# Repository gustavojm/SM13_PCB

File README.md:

# New Fixture Controller #
* Autor: DEEE
* GSPC

Poncho para la CIAA NXP con los RDC

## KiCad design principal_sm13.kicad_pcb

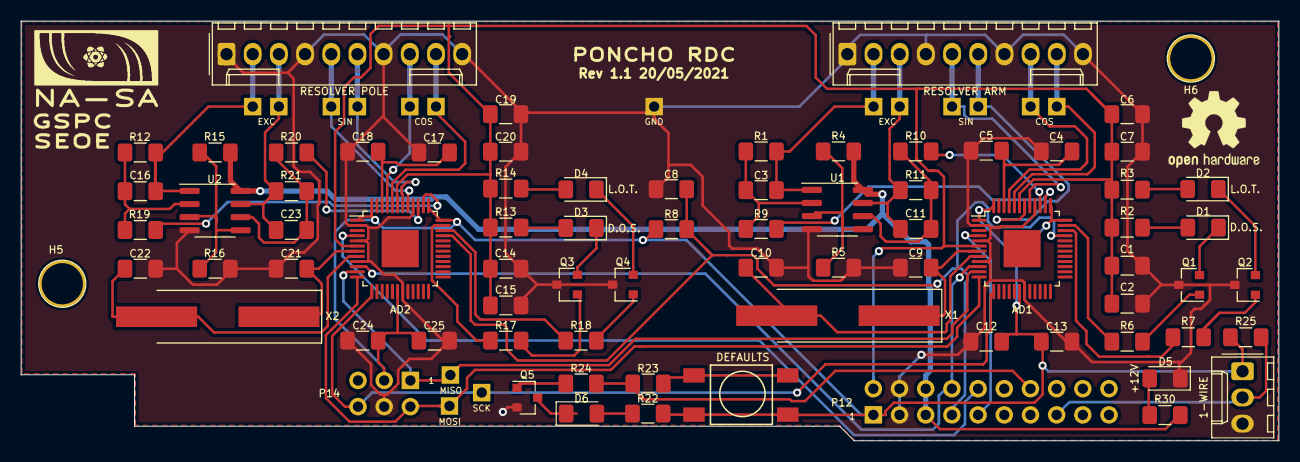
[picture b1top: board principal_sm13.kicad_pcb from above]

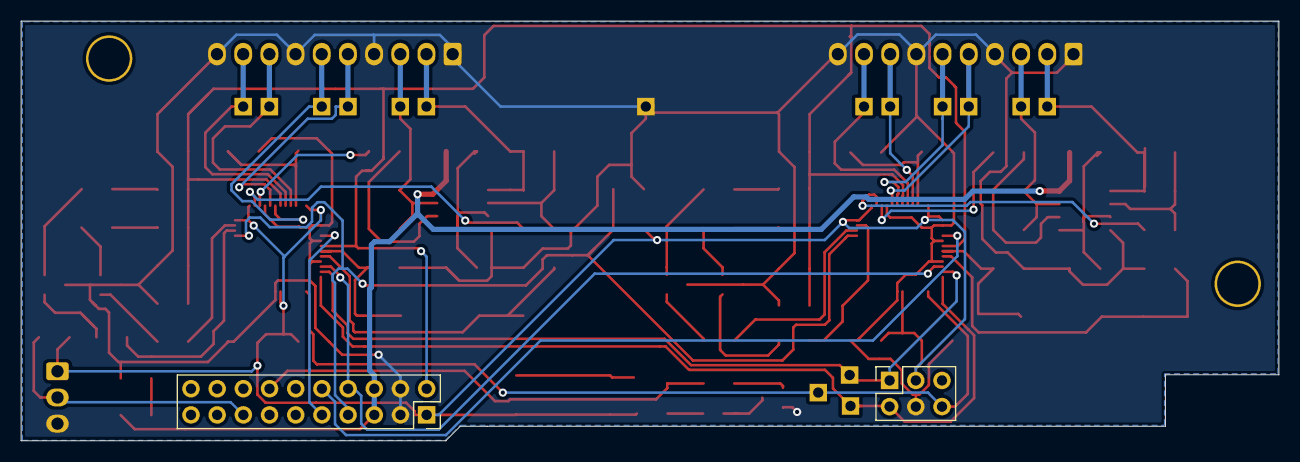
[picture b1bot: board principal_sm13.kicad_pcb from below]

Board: 2 copper layers, 122.0 x 40.7 mm, 93 parts (2 on the bottom side), 62 nets.

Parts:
AD1, AD2: AD2S1210; LQFP-48-1EP_7x7mm_P0.5mm_EP3.6x3.6mm
C1, C7, C13, C14, C20, C25: 4,7µ; C_1206_3216Metric_Pad1.42x1.75mm_HandSolder
C2, C4, C6, C12, C15, C17, C19, C24: 10n; C_1206_3216Metric_Pad1.42x1.75mm_HandSolder
C3, C11, C16, C23: 120p; C_1206_3216Metric_Pad1.42x1.75mm_HandSolder
C5, C18: 10µ; C_1206_3216Metric_Pad1.42x1.75mm_HandSolder
C8: 100n; C_1206_3216Metric_Pad1.42x1.75mm_HandSolder
C9, C10, C21, C22: 20p; C_1206_3216Metric_Pad1.42x1.75mm_HandSolder
D1, D2, D3, D4, D5, D6: LED; LED_1206_3216Metric_Pad1.42x1.75mm_HandSolder
H5, H6: 4mm; 1pin
J1: RESOLVER ARM; Molex_KK-254_AE-6410-10A_1x10_P2.54mm_Vertical
J2: RESOLVER POLE; Molex_KK-254_AE-6410-10A_1x10_P2.54mm_Vertical
J3: 1-WIRE; Molex_KK-254_AE-6410-03A_1x03_P2.54mm_Vertical
LOGO: logo_nasa
P12: CONN_10X2; PinSocket_2x10_P2.54mm_Vertical
P14: SPI; PinSocket_2x03_P2.54mm_Vertical
Q1, Q2, Q3, Q4: BC807; SOT-23
Q5: BC817; SOT-23
R1, R11, R12, R21: 12K; R_1206_3216Metric_Pad1.42x1.75mm_HandSolder
R2, R3, R13, R14, R22: 120; R_1206_3216Metric_Pad1.42x1.75mm_HandSolder
R4, R15: 22K; R_1206_3216Metric_Pad1.42x1.75mm_HandSolder
R5, R8, R9, R10, R16, R19, R20: 10K; R_1206_3216Metric_Pad1.42x1.75mm_HandSolder
R6, R7, R17, R18, R23, R24: 1K; R_1206_3216Metric_Pad1.42x1.75mm_HandSolder
R25: 4,7K; R_1206_3216Metric_Pad1.42x1.75mm_HandSolder
R30: 560; R_1206_3216Metric_Pad1.42x1.75mm_HandSolder
SW1: DEFAULTS; PUSH_SWITCH
TP1: TP_SCK; TestPoint_reducido
TP2: TP_MOSI; TestPoint_reducido
TP3: TP_MISO; TestPoint_reducido
TP4: TPCOSARM; TestPoint_reducido
TP5: TPCOSLOARM; TestPoint_reducido
TP6: TPSINLOARM; TestPoint_reducido
TP7: TPSINARM; TestPoint_reducido
TP8: TPEXCARM; TestPoint_reducido
TP9: TPEXCLOARM; TestPoint_reducido
TP10: TPCOSPOLE; TestPoint_reducido
TP11: TPCOSLOPOLE; TestPoint_reducido
TP12: TPSINLOPOLE; TestPoint_reducido
TP13: TPSINPOLE; TestPoint_reducido
TP14: TPEXCPOLE; TestPoint_reducido
TP15: TPEXCLOPOLE; TestPoint_reducido
TP16: TPGND; TestPoint_reducido
U1, U2: AD8397ARZ; SOIC-8_3.9x4.9mm_P1.27mm
X1, X2: 8.192MHz; Crystal_SMD_HC49-SD_HandSoldering

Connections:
+3V3: AD1.1, AD1.18, AD1.36, AD1.37, AD1.48, AD2.1, AD2.18, AD2.36, AD2.37, AD2.48, C12.1, C13.1, C24.1, C25.1, J3.1, P12.1, P14.3, R8.1, R22.1, R25.1, SW1.1, SW1.2
+5V: AD1.6, AD1.43, AD2.6, AD2.43, C1.1, C2.1, C6.2, C7.1, C14.1, C15.1, C19.2, C20.1, P12.2, R2.1, R3.1, R13.1, R14.1
+12V: P12.5, P12.6, R4.2, R15.2, R30.1, U1.8, U2.8
/GPIO/GPIO0: AD1.33, AD2.33, C8.1, P12.7, R8.2
/GPIO/GPIO1: AD1.10, AD2.10, P12.8
/GPIO/GPIO2: AD1.4, P12.9
/GPIO/GPIO3: AD2.4, P12.10
/GPIO/GPIO7: P12.14, R23.2, R24.2
/GPIO/GPIO8: J3.2, P12.15, R25.2
/GPIO/SPI_SCK: AD1.13, AD2.13, P14.6, TP1.1
/RDC ARM/COS: AD1.45, J1.8, TP4.1
/RDC ARM/COSLO: AD1.44, J1.9, TP5.1
/RDC ARM/EXC: AD1.38, R9.1
/RDC ARM/MISO: AD1.11, AD2.11, P14.1, TP3.1
/RDC ARM/MOSI: AD1.12, AD2.12, P14.2, TP2.1
/RDC ARM/SIN: AD1.41, J1.5, TP7.1
/RDC ARM/SINLO: AD1.42, J1.6, TP6.1
/RDC ARM/~EXC: AD1.39, R10.1
/RDC POLE/COS: AD2.45, J2.8, TP10.1
/RDC POLE/COSLO: AD2.44, J2.9, TP11.1
/RDC POLE/EXC: AD2.38, R19.1
/RDC POLE/SIN: AD2.41, J2.5, TP13.1
/RDC POLE/SINLO: AD2.42, J2.6, TP12.1
/RDC POLE/~EXC: AD2.39, R20.1
GND: AD1.2, AD1.5, AD1.9, AD1.19, AD1.40, AD2.2, AD2.5, AD2.9, AD2.19, AD2.40, C1.2, C2.2, C4.2, C5.2, C6.1, C7.2, C8.2, C9.2, C10.2, C12.2, C13.2, C14.2, C15.2, C17.2, C18.2, C19.1, C20.2, C21.2, C22.2, C24.2, C25.2, D5.1, J1.1, J1.4, J1.7, J1.10, J2.1, J2.4, J2.7, J2.10, J3.3, P12.3, P12.4, P14.4, Q1.3, Q2.3, Q3.3, Q4.3, Q5.2, R5.1, R16.1, TP16.1, U1.4, U2.4
unnamed: AD1.7, C9.1, X1.1
unnamed: AD1.8, C10.1, X1.2
unnamed: AD1.34, R7.2
unnamed: AD1.35, R6.2
unnamed: AD1.46, C4.1, C5.1
unnamed: AD2.7, C21.1, X2.1
unnamed: AD2.8, C22.1, X2.2
unnamed: AD2.34, R18.2
unnamed: AD2.35, R17.2
unnamed: AD2.46, C17.1, C18.1
unnamed: C3.1, J1.2, R1.1, TP8.1, U1.1
unnamed: C3.2, R1.2, R9.2, U1.2
unnamed: C11.1, J1.3, R11.1, TP9.1, U1.7
unnamed: C11.2, R10.2, R11.2, U1.6
unnamed: C16.1, J2.2, R12.1, TP14.1, U2.1
unnamed: C16.2, R12.2, R19.2, U2.2
unnamed: C23.1, J2.3, R21.1, TP15.1, U2.7
unnamed: C23.2, R20.2, R21.2, U2.6
unnamed: D1.1, Q1.2
unnamed: D1.2, R2.2
unnamed: D2.1, Q2.2
unnamed: D2.2, R3.2
unnamed: D3.1, Q3.2
unnamed: D3.2, R13.2
unnamed: D4.1, Q4.2
unnamed: D4.2, R14.2
unnamed: D5.2, R30.2
unnamed: D6.1, Q5.3
unnamed: D6.2, R22.2
unnamed: Q1.1, R6.1
unnamed: Q2.1, R7.1
unnamed: Q3.1, R17.1
unnamed: Q4.1, R18.1
unnamed: Q5.1, R24.1
unnamed: R4.1, R5.2, U1.3, U1.5
unnamed: R15.1, R16.2, U2.3, U2.5
unnamed: R23.1, SW1.3, SW1.4

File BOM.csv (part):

"Source:","/home/gustavo/SM13/Esquema/principal_sm13.sch"
"Date:","jue 20 ago 2020 00:38:13 -03"
"Tool:","Eeschema 5.1.6-c6e7f7d~86~ubuntu16.04.1"
"Generator:","/usr/share/kicad/plugins/bom_csv_grouped_by_value.py"
"Component Count:","66"

"Individual Components:"

"Item","Qty","Reference(s)","Value","LibPart","Footprint","Datasheet","Field4","Field5","Field6","Field7"
"","","AD1","AD2S1210","AD2S1210:AD2S1210","Package_QFP:LQFP-48-1EP_7x7mm_P0.5mm_EP3.6x3.6mm","","","","",""
"","","AD2","AD2S1210","AD2S1210:AD2S1210","Package_QFP:LQFP-48-1EP_7x7mm_P0.5mm_EP3.6x3.6mm","","","","",""
"","","C1","4,7µ","Device:C","Capacitor_SMD:C_1206_3216Metric_Pad1.42x1.75mm_HandSolder","~","","","",""
"","","C2","10n","Device:C","Capacitor_SMD:C_1206_3216Metric_Pad1.42x1.75mm_HandSolder","~","","","",""
"","","C3","120p","Device:C","Capacitor_SMD:C_1206_3216Metric_Pad1.42x1.75mm_HandSolder","~","","","",""
"","","C4","10n","Device:C","Capacitor_SMD:C_1206_3216Metric_Pad1.42x1.75mm_HandSolder","~","","","",""
"","","C5","10µ","Device:C","Capacitor_SMD:C_1206_3216Metric_Pad1.42x1.75mm_HandSolder","~","","","",""
"","","C6","10n","Device:C","Capacitor_SMD:C_1206_3216Metric_Pad1.42x1.75mm_HandSolder","~","","","",""
"","","C7","4,7µ","Device:C","Capacitor_SMD:C_1206_3216Metric_Pad1.42x1.75mm_HandSolder","~","","","",""
"","","C8","100n","Device:C","Capacitor_SMD:C_1206_3216Metric_Pad1.42x1.75mm_HandSolder","~","","","",""
"","","C9","20p","Device:C","Capacitor_SMD:C_1206_3216Metric_Pad1.42x1.75mm_HandSolder","~","","","",""
"","","C10","20p","Device:C","Capacitor_SMD:C_1206_3216Metric_Pad1.42x1.75mm_HandSolder","~","","","",""
"","","C11","120p","Device:C","Capacitor_SMD:C_1206_3216Metric_Pad1.42x1.75mm_HandSolder","~","","","",""
"","","C12","10n","Device:C","Capacitor_SMD:C_1206_3216Metric_Pad1.42x1.75mm_HandSolder","~","","","",""
"","","C13","4,7µ","Device:C","Capacitor_SMD:C_1206_3216Metric_Pad1.42x1.75mm_HandSolder","~","","","",""
"","","C14","4,7µ","Device:C","Capacitor_SMD:C_1206_3216Metric_Pad1.42x1.75mm_HandSolder","~","","","",""
"","","C15","10n","Device:C","Capacitor_SMD:C_1206_3216Metric_Pad1.42x1.75mm_HandSolder","~","","","",""
"","","C16","120p","Device:C","Capacitor_SMD:C_1206_3216Metric_Pad1.42x1.75mm_HandSolder","~","","","",""
"","","C17","10n","Device:C","Capacitor_SMD:C_1206_3216Metric_Pad1.42x1.75mm_HandSolder","~","","","",""
"","","C18","10µ","Device:C","Capacitor_SMD:C_1206_3216Metric_Pad1.42x1.75mm_HandSolder","~","","","",""
"","","C19","10n","Device:C","Capacitor_SMD:C_1206_3216Metric_Pad1.42x1.75mm_HandSolder","~","","","",""
"","","C20","4,7µ","Device:C","Capacitor_SMD:C_1206_3216Metric_Pad1.42x1.75mm_HandSolder","~","","","",""
"","","C21","20p","Device:C","Capacitor_SMD:C_1206_3216Metric_Pad1.42x1.75mm_HandSolder","~","","","",""
"","","C22","20p","Device:C","Capacitor_SMD:C_1206_3216Metric_Pad1.42x1.75mm_HandSolder","~","","","",""
"","","C23","120p","Device:C","Capacitor_SMD:C_1206_3216Metric_Pad1.42x1.75mm_HandSolder","~","","","",""
"","","C24","10n","Device:C","Capacitor_SMD:C_1206_3216Metric_Pad1.42x1.75mm_HandSolder","~","","","",""
"","","C25","4,7µ","Device:C","Capacitor_SMD:C_1206_3216Metric_Pad1.42x1.75mm_HandSolder","~","","","",""
"","","D1","LED","Device:LED","LED_SMD:LED_1206_3216Metric_Pad1.42x1.75mm_HandSolder","~","","","",""
"","","D2","LED","Device:LED","LED_SMD:LED_1206_3216Metric_Pad1.42x1.75mm_HandSolder","~","","","",""
"","","D3","LED","Device:LED","LED_SMD:LED_1206_3216Metric_Pad1.42x1.75mm_HandSolder","~","","","",""
"","","D4","LED","Device:LED","LED_SMD:LED_1206_3216Metric_Pad1.42x1.75mm_HandSolder","~","","","",""
"","","D5","LED","Device:LED","LED_SMD:LED_1206_3216Metric_Pad1.42x1.75mm_HandSolder","~","","","",""
"","","J1","RESOLVER ARM","Connector_Generic:Conn_01x10","Connector_Molex:Molex_KK-254_AE-6410-10A_1x10_P2.54mm_Vertical","~","","","",""
"","","J2","RESOLVER POLE","Connector_Generic:Conn_01x10","Connector_Molex:Molex_KK-254_AE-6410-10A_1x10_P2.54mm_Vertical","~","","","",""
"","","P12","CONN_10X2","conn_10x2:CONN_10X2","Connector_PinSocket_2.54mm:PinSocket_2x10_P2.54mm_Vertical","","","","",""
"","","P14","SPI","conn_3x2:CONN_3X2","Connector_PinSocket_2.54mm:PinSocket_2x03_P2.54mm_Vertical","","","","",""
"","","Q1","BC807","Transistor_BJT:BC807","Package_TO_SOT_SMD:SOT-23","http://www.fairchildsemi.com/ds/BC/BC807.pdf","","","",""
"","","Q2","BC807","Transistor_BJT:BC807","Package_TO_SOT_SMD:SOT-23","http://www.fairchildsemi.com/ds/BC/BC807.pdf","","","",""
"","","Q3","BC807","Transistor_BJT:BC807","Package_TO_SOT_SMD:SOT-23","http://www.fairchildsemi.com/ds/BC/BC807.pdf","","","",""
"","","Q4","BC807","Transistor_BJT:BC807","Package_TO_SOT_SMD:SOT-23","http://www.fairchildsemi.com/ds/BC/BC807.pdf","","","",""
"","","R1","12K","Device:R","Resistor_SMD:R_1206_3216Metric_Pad1.42x1.75mm_HandSolder","~","","","",""
"","","R2","120","Device:R","Resistor_SMD:R_1206_3216Metric_Pad1.42x1.75mm_HandSolder","~","","","",""
"","","R3","120","Device:R","Resistor_SMD:R_1206_3216Metric_Pad1.42x1.75mm_HandSolder","~","","","",""
"","","R4","22K","Device:R","Resistor_SMD:R_1206_3216Metric_Pad1.42x1.75mm_HandSolder","~","","","",""
"","","R5","10K","Device:R","Resistor_SMD:R_1206_3216Metric_Pad1.42x1.75mm_HandSolder","~","","","",""
"","","R6","1K","Device:R","Resistor_SMD:R_1206_3216Metric_Pad1.42x1.75mm_HandSolder","~","","","",""
"","","R7","1K","Device:R","Resistor_SMD:R_1206_3216Metric_Pad1.42x1.75mm_HandSolder","~","","","",""
"","","R8","10K","Device:R","Resistor_SMD:R_1206_3216Metric_Pad1.42x1.75mm_HandSolder","~","","","",""
"","","R9","10K","Device:R","Resistor_SMD:R_1206_3216Metric_Pad1.42x1.75mm_HandSolder","~","","","",""
"","","R10","10K","Device:R","Resistor_SMD:R_1206_3216Metric_Pad1.42x1.75mm_HandSolder","~","","","",""
"","","R11","12K","Device:R","Resistor_SMD:R_1206_3216Metric_Pad1.42x1.75mm_HandSolder","~","","","",""
"","","R12","12K","Device:R","Resistor_SMD:R_1206_3216Metric_Pad1.42x1.75mm_HandSolder","~","","","",""
"","","R13","120","Device:R","Resistor_SMD:R_1206_3216Metric_Pad1.42x1.75mm_HandSolder","~","","","",""
"","","R14","120","Device:R","Resistor_SMD:R_1206_3216Metric_Pad1.42x1.75mm_HandSolder","~","","","",""
"","","R15","22K","Device:R","Resistor_SMD:R_1206_3216Metric_Pad1.42x1.75mm_HandSolder","~","","","",""
"","","R16","10K","Device:R","Resistor_SMD:R_1206_3216Metric_Pad1.42x1.75mm_HandSolder","~","","","",""
"","","R17","1K","Device:R","Resistor_SMD:R_1206_3216Metric_Pad1.42x1.75mm_HandSolder","~","","","",""
"","","R18","1K","Device:R","Resistor_SMD:R_1206_3216Metric_Pad1.42x1.75mm_HandSolder","~","","","",""
"","","R19","10K","Device:R","Resistor_SMD:R_1206_3216Metric_Pad1.42x1.75mm_HandSolder","~","","","",""
"","","R20","10K","Device:R","Resistor_SMD:R_1206_3216Metric_Pad1.42x1.75mm_HandSolder","~","","","",""
"","","R21","12K","Device:R","Resistor_SMD:R_1206_3216Metric_Pad1.42x1.75mm_HandSolder","~","","","",""
"","","R30","560","Device:R","Resistor_SMD:R_1206_3216Metric_Pad1.42x1.75mm_HandSolder","~","","","",""
"","","U1","AD8397ARZ","AD8397ARZ:AD8397ARZ","Package_SO:SOIC-8_3.9x4.9mm_P1.27mm","Analog Devices","AD8397ARZ","1078284","19M1201","SOIC-8"
"","","U2","AD8397ARZ","AD8397ARZ:AD8397ARZ","Package_SO:SOIC-8_3.9x4.9mm_P1.27mm","Analog Devices","AD8397ARZ","1078284","19M1201","SOIC-8"
"","","X1","8.192MHz","Device:Crystal","Crystal:Crystal_SMD_HC49-SD_HandSoldering","~","","","",""
"","","X2","8.192MHz","Device:Crystal","Crystal:Crystal_SMD_HC49-SD_HandSoldering","~","","","",""



"Collated Components:"

"Item","Qty","Reference(s)","Value","LibPart","Footprint","Datasheet","Field4","Field5","Field6","Field7"
"1","2","AD1, AD2","AD2S1210","AD2S1210:AD2S1210","Package_QFP:LQFP-48-1EP_7x7mm_P0.5mm_EP3.6x3.6mm","","","","",""
"2","6","C1, C7, C13, C14, C20, C25","4,7µ","Device:C","Capacitor_SMD:C_1206_3216Metric_Pad1.42x1.75mm_HandSolder","~","","","",""
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
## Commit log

2020-06-24 Commit inicial
2020-06-25 resolución fijada en 16 bits y modo configuración fijado
2020-07-03 agregado el segundo RDC, leds conectados a +5v, asignados footprints
2020-07-04 componentes alineados
2020-07-04 cambios en el placement
2020-07-04 componentes montados sobre placa CIAA NXP para hacer el sandwich
2020-07-06 reubicados componentes, cambiado regulador a SMD
2020-07-06 routeado completo, quedan 32 vias
2020-07-07 reducida la placa para que queden libres los conectores de la CIAA, ruteado completo, quedan 38 vias
2020-07-07 agregadas zonas de relleno conecadas a GND
2020-07-07 agregados test points parara comunicacion SPI, ruteado, 28 vias
2020-07-07 el freerouting no conecta bien si hay zonas llenas, 30 vias
2020-07-07 preliminar, 30 vias
2020-07-08 cambiados conectores, agregado conversor 3,3->TTL drivers
2020-07-08 ajustada el area contra los reles
2020-07-08 cambiado a conectores MOLEX KK, agregados test points para señales analogicas
2020-07-14 outline reducido, para revision por peers
2020-07-15 eliminado regulador 12v, alimentar CIAA con 12v directamente
2020-07-16 cambiados capacitores electroliticos por tantalio (unpolarized). Agrandado footprint test pads, generado BOM, 35 vias
2020-07-17 agrandados pads de test points
2020-07-17 agregado logo OSHW y nomy nombre poncho
2020-07-17 movido texto poncho y alejada pista alrededor de H6
2020-07-28 modificado cambiador de nivel de salida, agregados TP para los gpio STEP y DIRECTION de los motore PAP
2020-07-28 regenerado BOM
2020-07-28 alejadas algunas pistas, thermal pads clearance = 0
2020-07-31 agrandado tipo letra leyendas, generados archivos Gerber de fabricación
2020-08-20 eliminado gpio para motores ya que la CIAA no cuenta con suficientes GPIOs disponibles. Se usara DOUTS
2021-05-21 Se arregló conexion erronea en los amplificadores operacionales
    se agregó conexión 1-wire en GPIO8
    se agregó botón y led que comparten GPIO7, la idea es leer el estado del
    botón y al liberarlo cambiar el GPIO a output y encender el led indicando
    alguna acción
